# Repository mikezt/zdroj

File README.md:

# RD35-A power supply

This repository contain KiCAD project with small board to connect MW RD35-A power supply to 230V and various output connectors. The power supply is cased in [1594ESGY case](https://www.reichelt.de/universalgehaeuse-serie-1594-107-x-167-x-53-mm-grau-1594esgy-p221318.html?&trstct=pos_7&nbc=1).

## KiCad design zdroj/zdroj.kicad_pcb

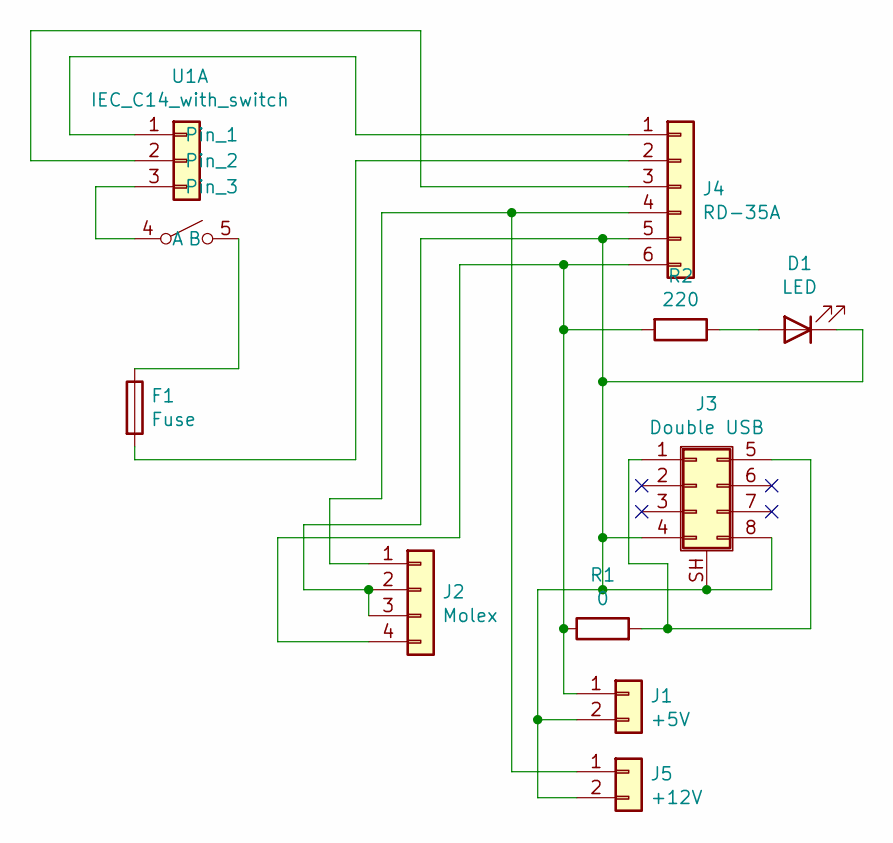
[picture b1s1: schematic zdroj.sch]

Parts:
D1: LED; LED_D3.0mm
F1: Fuse; Fuseholder_Cylinder-5x20mm_Stelvio-Kontek_PTF78_Horizontal_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
J1: +5V; PinSocket_1x02_P2.54mm_Vertical
J2: Molex; TE_MATE-N-LOK_350211-1_1x04_P5.08mm_Vertical
J3: Double USB; USB_A_Wuerth_61400826021_Horizontal_Stacked
J4: RD-35A; SolderWire-0.5sqmm_1x06_P4.8mm_D0.9mm_OD2.3mm
J5: +12V; PinSocket_1x02_P2.54mm_Vertical
R1: 0; R_Axial_DIN0411_L9.9mm_D3.6mm_P20.32mm_Horizontal
R2: 220; R_Axial_DIN0411_L9.9mm_D3.6mm_P20.32mm_Horizontal
U1: IEC_C14_with_switch; Connector_EIC_C14_with_switch

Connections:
unnamed: D1.1 (K), J1.2, J2.2, J2.3, J3.4, J3.8, J3.SH (Shield), J4.5, J5.2
unnamed: D1.2 (A), R2.1
unnamed: F1.1, U1.5 (B)
unnamed: F1.2, J4.2
unnamed: J1.1, J2.4, J4.6, R1.1, R2.2
unnamed: J2.1, J4.4, J5.1
unnamed: J3.1, J3.5, R1.2
unnamed: J4.1, U1.1
unnamed: J4.3, U1.2
unnamed: U1.3, U1.4 (A)

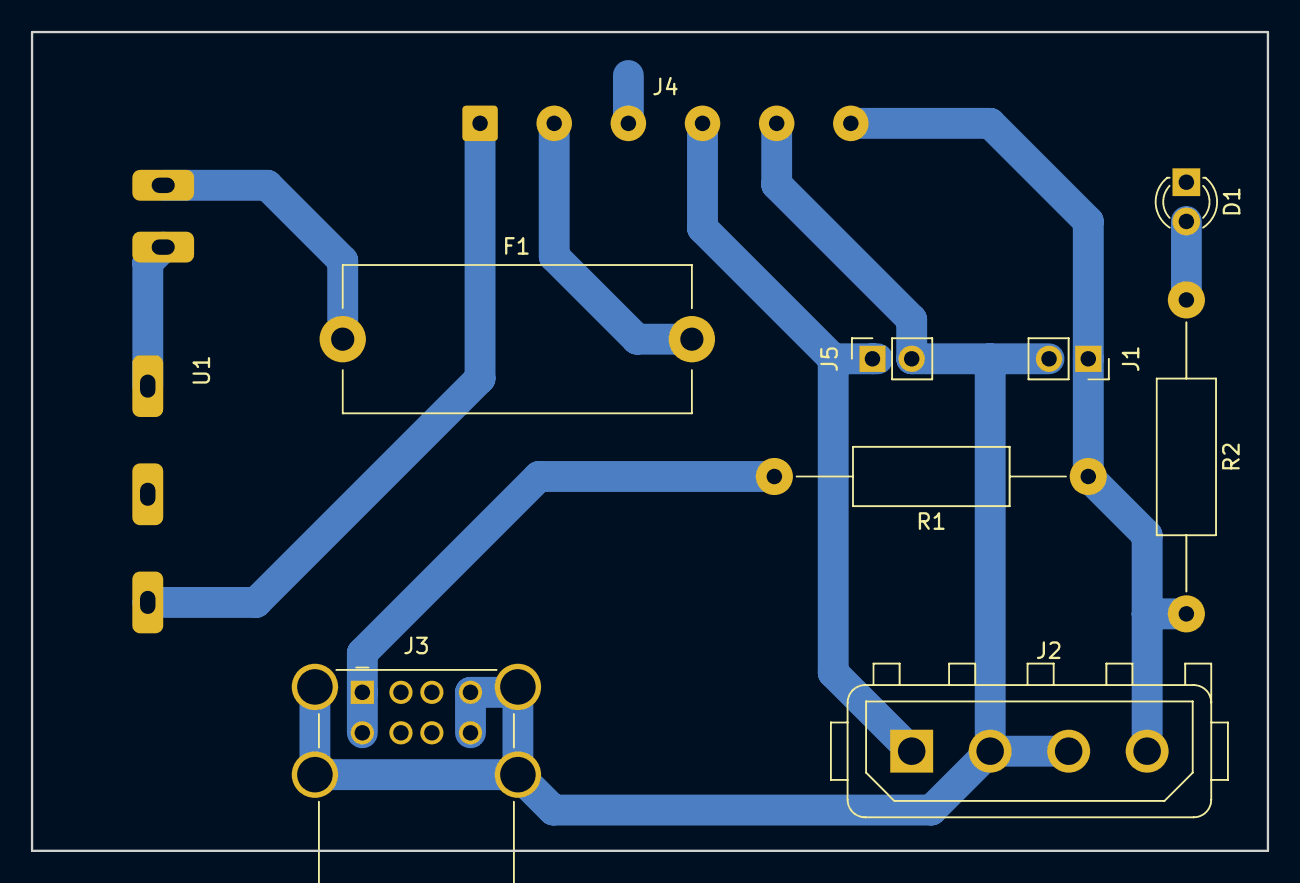
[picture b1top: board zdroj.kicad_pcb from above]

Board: 2 copper layers, 80.0 x 53.0 mm, 10 parts (0 on the bottom side), 10 nets.

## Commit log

2021-05-28 fill the repository with all the nice files
2021-05-29 update README, add pictures
